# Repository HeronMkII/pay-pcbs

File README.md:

# Payload Subsystem PCBs
**PAY SSM V2**
**PAY LED V1**
**PAY SENSOR V1**

Schematic & PCB layout files for the Payload SSM. 

Layout done in KiCad.

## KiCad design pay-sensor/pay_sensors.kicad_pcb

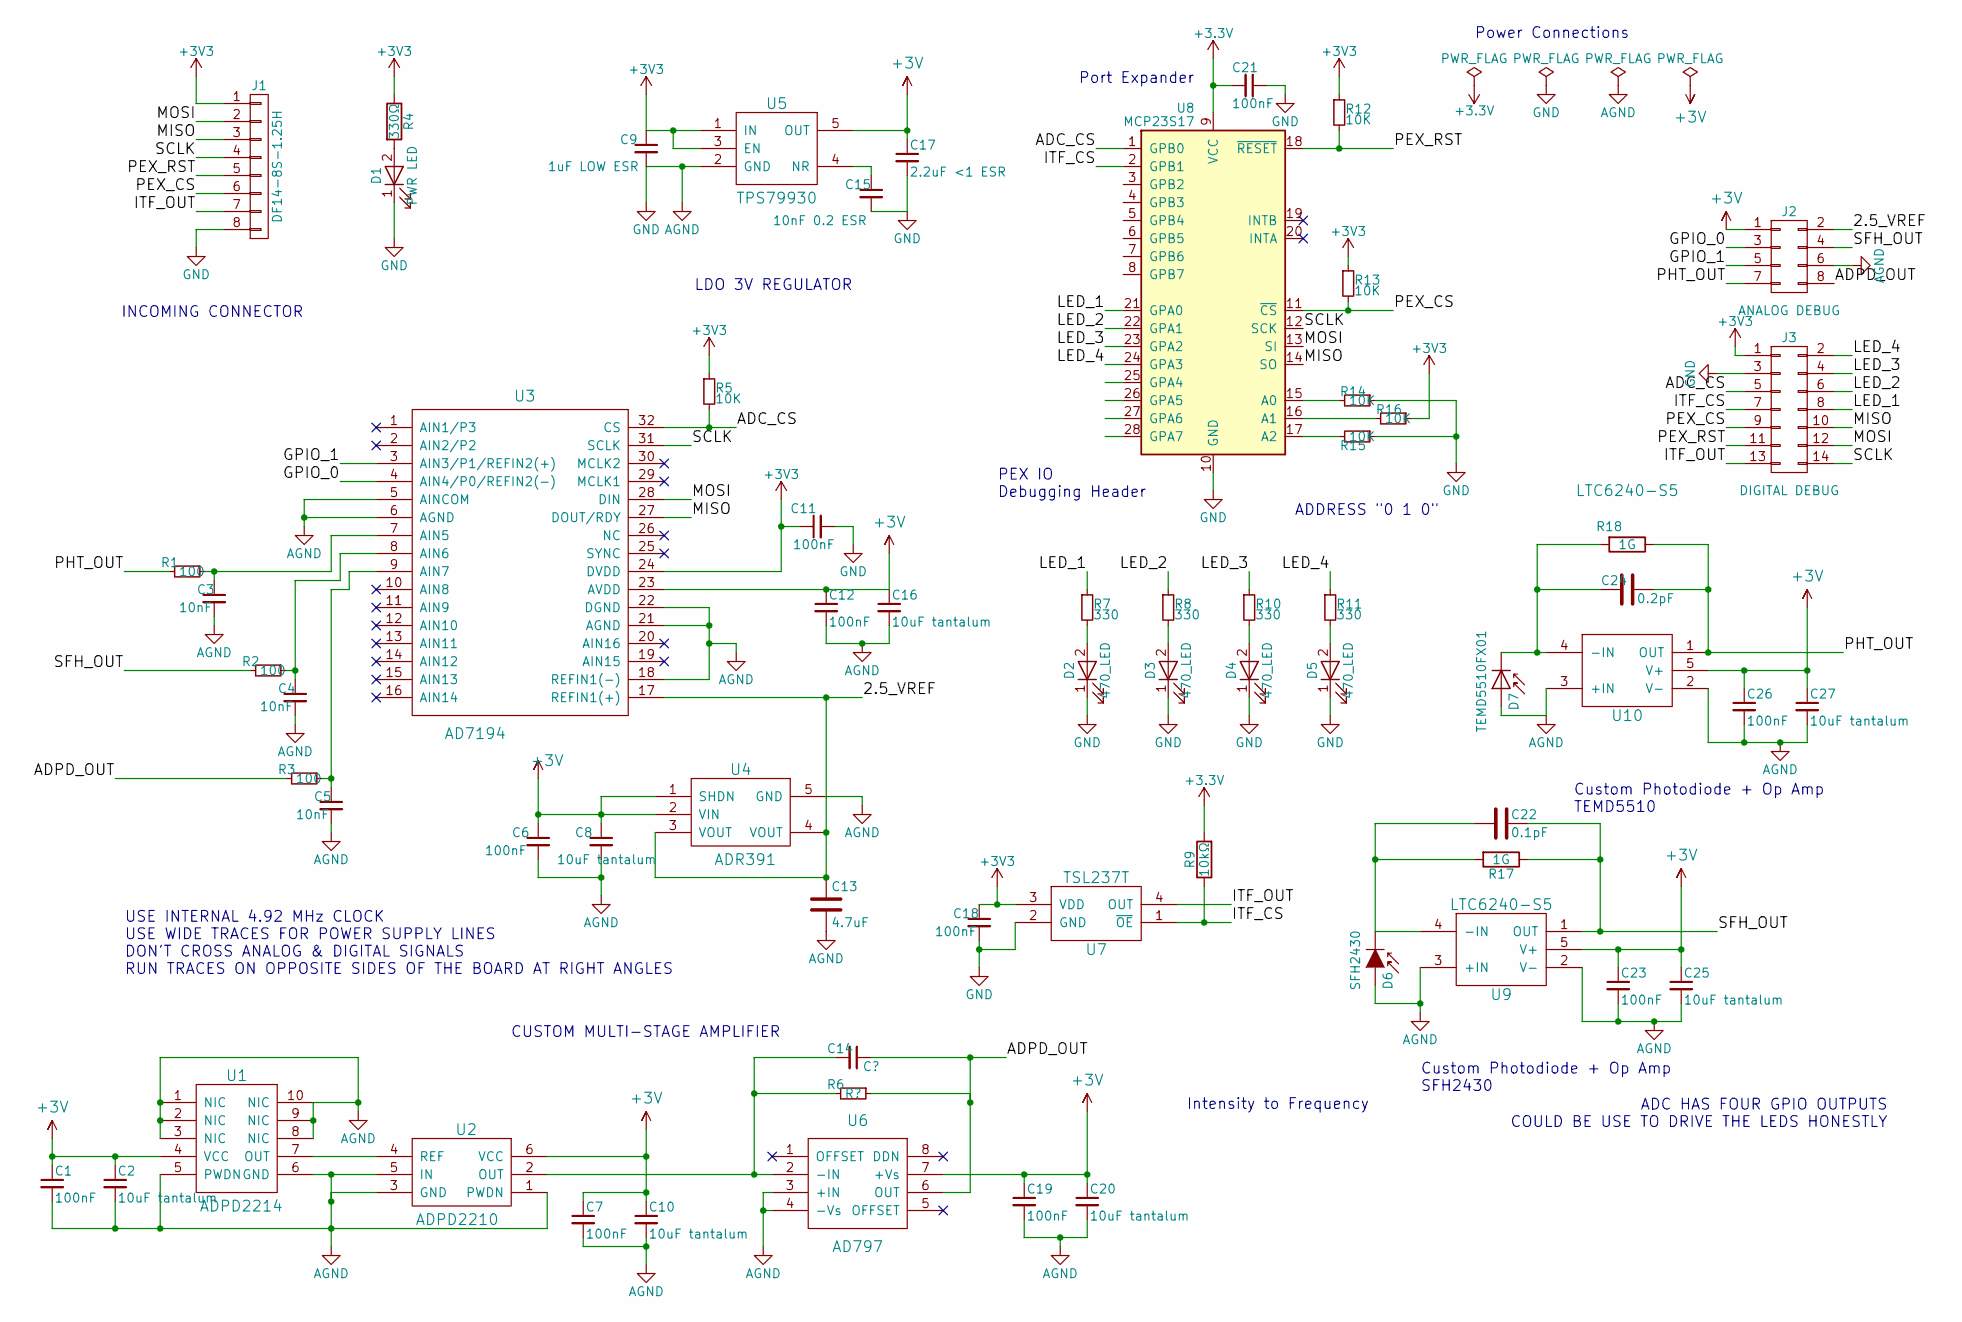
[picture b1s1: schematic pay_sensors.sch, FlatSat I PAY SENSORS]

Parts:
C1, C6, C7, C11, C12, C18, C19, C21, C23, C26: 100nF; C_0603
C2, C8, C10, C16, C20, C25, C27: 10uF tantalum; C_0603
C3, C4, C5: 10nF; C_0603
C9: 1uF LOW ESR; C_0603
C13: 4.7uF; C_0603
C14: C?; C_0603
C15: 10nF 0.2 ESR; C_0603
C17: 2.2uF <1 ESR; C_0603
C22: 0.1pF; C_0603
C24: 0.2pF; C_0603
D1: PWR LED; LED_0603
D2, D3, D4, D5: 470_LED; LED_0603
D6: SFH2430
D7: TEMD5510FX01; TEMD5510
J1: DF14-8S-1.25H; Hirose_DF14-8P-1.25H
J2: ANALOG DEBUG; Socket_Strip_Straight_2x04_Pitch2.54mm
J3: DIGITAL DEBUG; Socket_Strip_Straight_2x07_Pitch2.54mm
R1, R2, R3: 100; R_0603
R4: 330Ω; R_0603
R5, R12, R13, R14, R15, R16: 10K; R_0603
R6: R?; R_0603
R7, R8, R10, R11: 330; R_0603
R9: 10kΩ; R_0603
R17, R18: 1G; R_0603
U1: ADPD2214
U2: ADPD2210
U3: AD7194; QFN-32-1EP_5x5mm_Pitch0.5mm
U4: ADR391; SOT-23-5
U5: TPS79930; SOT-23-5
U6: AD797; SOIC-8_3.9x4.9mm_Pitch1.27mm
U7: TSL237T
U8: MCP23S17; SSOP-28_5.3x10.2mm_Pitch0.65mm
U9, U10: LTC6240-S5; SOT-23-5

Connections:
+3V: C1.1, C2.1, C6.1, C7.1, C8.1, C10.1, C12.1, C16.1, C17.1, C19.1, C20.1, C23.1, C25.1, C26.1, C27.1, J2.1, U1.4 (VCC), U2.6 (VCC), U3.23 (AVDD), U4.1 (SHDN), U4.2 (VIN), U5.5 (OUT), U6.7 (+Vs), U9.5 (V+), U10.5 (V+)
/2.5_VREF: C13.1, J2.2, U3.17 (REFIN1(+)), U4.3 (VOUT), U4.4 (VOUT)
/ADC_CS: J3.5, R5.2, U3.32 (CS), U8.1 (GPB0)
/ADPD_OUT: C14.1, J2.8, R3.2, R6.1, U6.6 (OUT)
/GPIO_0: J2.3, U3.4 (AIN4/P0/REFIN2(-))
/GPIO_1: J2.5, U3.3 (AIN3/P1/REFIN2(+))
/ITF_CS: J3.7, R9.1, U7.1 (~OE), U8.2 (GPB1)
/ITF_OUT: J1.7, J3.13, U7.4 (OUT)
/LED_1: J3.8, R7.1, U8.21 (GPA0)
/LED_2: J3.6, R8.1, U8.22 (GPA1)
/LED_3: J3.4, R10.1, U8.23 (GPA2)
/LED_4: J3.2, R11.1, U8.24 (GPA3)
/MISO: J1.3, J3.10, U3.27 (DOUT/RDY), U8.14 (SO)
/MOSI: J1.2, J3.12, U3.28 (DIN), U8.13 (SI)
/PEX_CS: J1.6, J3.9, R13.2, U8.11 (~CS)
/PEX_RST: J1.5, J3.11, R12.2, U8.18 (~RESET)
/PHT_OUT: C24.1, J2.7, R1.2, R18.1, U10.1 (OUT)
/SCLK: J1.4, J3.14, U3.31 (SCLK), U8.12 (SCK)
/SFH_OUT: C22.1, J2.4, R2.2, R17.1, U9.1 (OUT)
AGND: C1.2, C2.2, C3.2, C4.2, C5.2, C6.2, C7.2, C8.2, C9.2, C10.2, C11.2, C12.2, C13.2, C15.2, C16.2, C17.2, C18.2, C19.2, C20.2, C21.1, C23.2, C25.2, C26.2, C27.2, D1.1 (K), D2.1 (K), D3.1 (K), D4.1 (K), D5.1 (K), D6.2 (A), D7.2 (A), J1.8, J2.6, J3.3, R14.1, R15.1, U1.1 (NIC), U1.2 (NIC), U1.3 (NIC), U1.5 (PWDN), U1.6 (GND), U1.8 (NIC), U1.9 (NIC), U1.10 (NIC), U2.1 (PWDN), U2.3 (GND), U2.5 (IN), U3.5 (AINCOM), U3.6 (AGND), U3.18 (REFIN1(-)), U3.21 (AGND), U3.22 (DGND), U4.5 (GND), U5.2 (GND), U6.3 (+IN), U6.4 (-Vs), U7.2 (GND), U8.10 (GND), U9.2 (V-), U9.3 (+IN), U10.2 (V-), U10.3 (+IN)
unnamed: C3.1, R1.1, U3.7 (AIN5)
unnamed: C4.1, R2.1, U3.8 (AIN6)
unnamed: C5.1, R3.1, U3.9 (AIN7)
unnamed: C14.2, R6.2, U2.2 (OUT), U6.2 (-IN)
unnamed: C15.1, U5.4 (NR)
unnamed: C22.2, D6.1 (K), R17.2, U9.4 (-IN)
unnamed: C24.2, D7.1 (K), R18.2, U10.4 (-IN)
unnamed: D1.2 (A), R4.2
unnamed: D2.2 (A), R7.2
unnamed: D3.2 (A), R8.2
unnamed: D4.2 (A), R10.2
unnamed: D5.2 (A), R11.2
unnamed: R14.2, U8.15 (A0)
unnamed: R15.2, U8.17 (A2)
unnamed: R16.2, U8.16 (A1)
unnamed: U1.7 (OUT), U2.4 (REF)

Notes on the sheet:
Port Expander
Power Connections
Custom Photodiode + Op Amp TEMD5510
PEX IO Debugging Header
ADDRESS "0 1 0"
INCOMING CONNECTOR
LDO 3V REGULATOR
USE INTERNAL 4.92 MHz CLOCK USE WIDE TRACES FOR POWER SUPPLY LINES DON'T CROSS ANALOG & DIGITAL SIGNALS RUN TRACES ON OPPOSITE SIDES OF THE BOARD AT RIGHT ANGLES
CUSTOM MULTI-STAGE AMPLIFIER
ADC HAS FOUR GPIO OUTPUTS COULD BE USE TO DRIVE THE LEDS HONESTLY
Custom Photodiode + Op Amp SFH2430
Intensity to Frequency

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
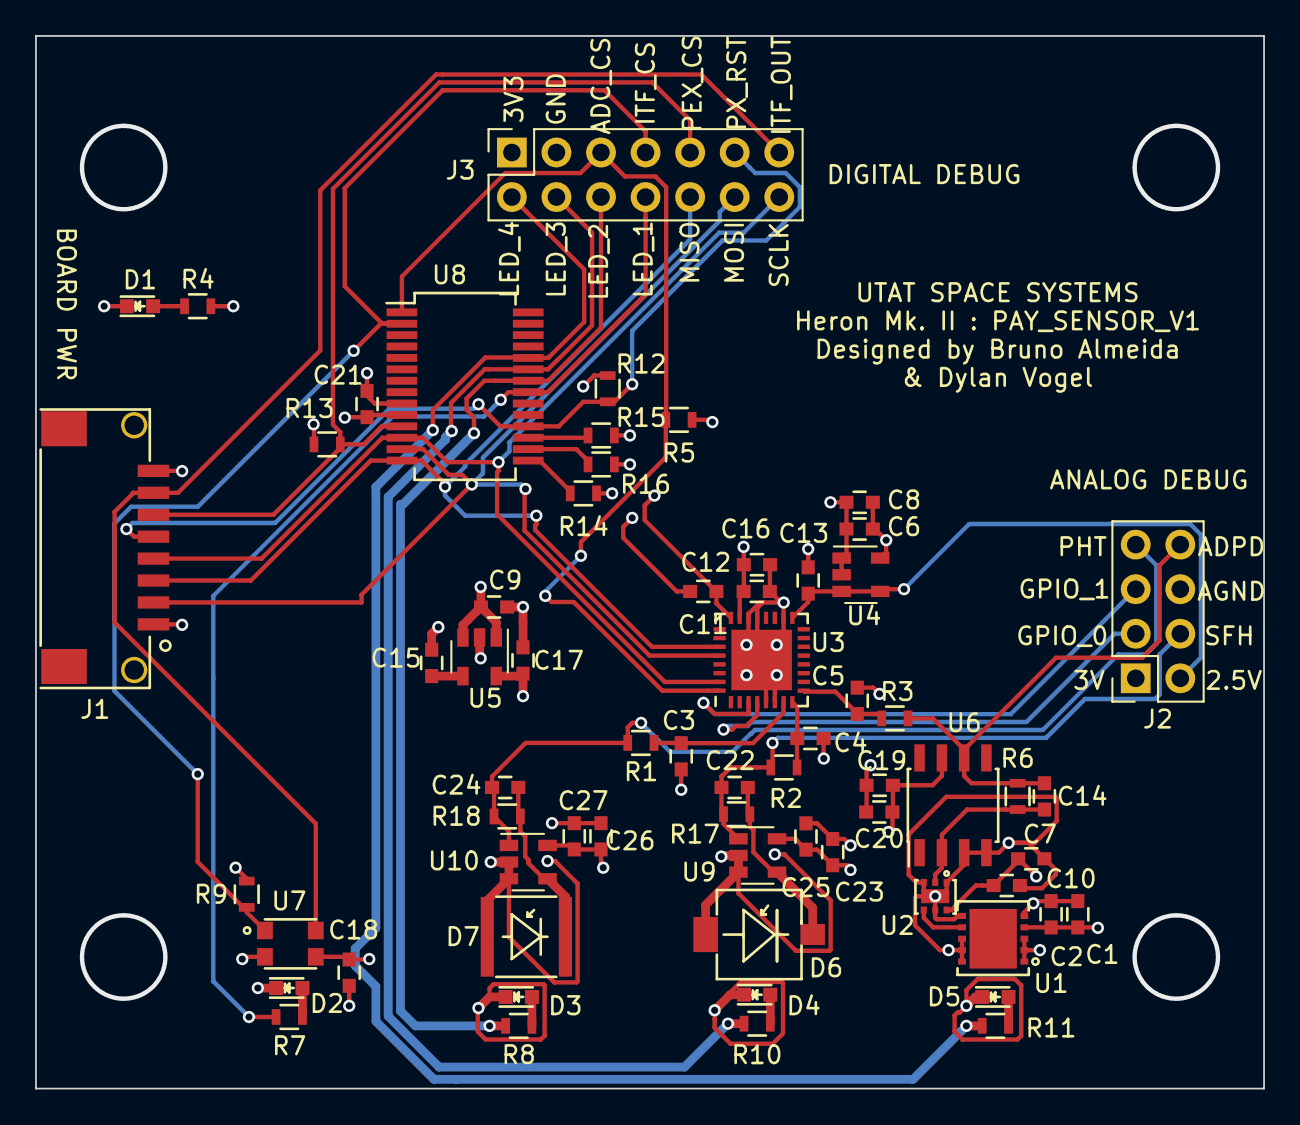
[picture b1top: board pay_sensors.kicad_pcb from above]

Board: 4 copper layers, 70.0 x 60.0 mm, 65 parts (0 on the bottom side), 37 nets.

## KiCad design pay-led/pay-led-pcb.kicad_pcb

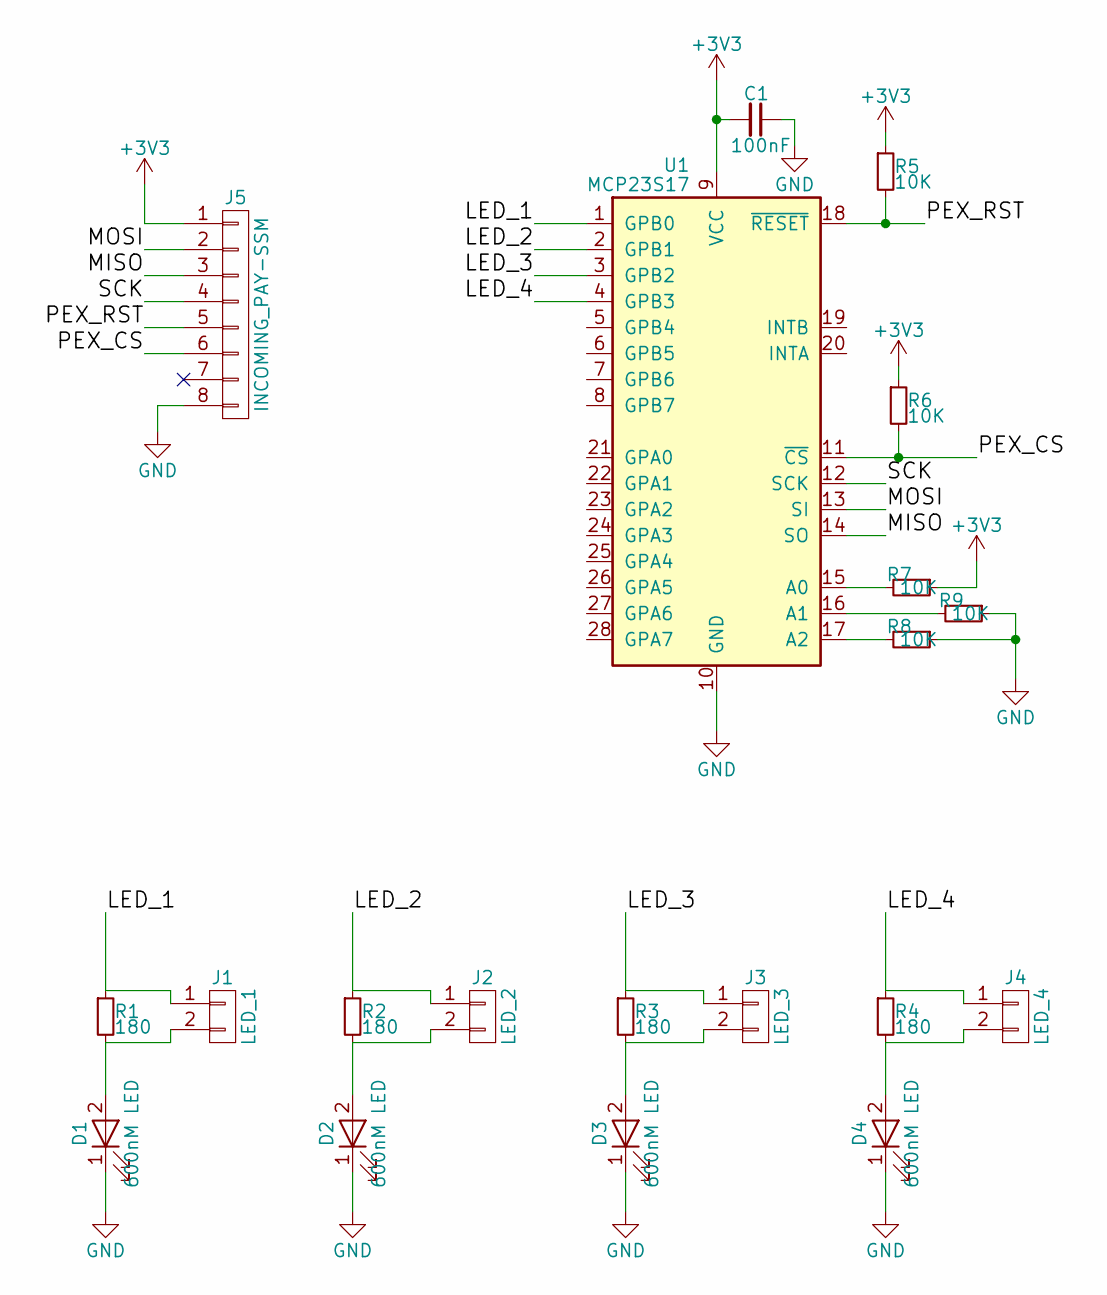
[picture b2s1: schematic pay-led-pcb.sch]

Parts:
C1: 100nF; C_0603
D1, D2, D3, D4: 600nM LED; LED_0603
J1: LED_1; Socket_Strip_Straight_1x02_Pitch2.54mm
J2: LED_2; Socket_Strip_Straight_1x02_Pitch2.54mm
J3: LED_3; Socket_Strip_Straight_1x02_Pitch2.54mm
J4: LED_4; Socket_Strip_Straight_1x02_Pitch2.54mm
J5: INCOMING_PAY-SSM; Hirose_DF14-8P-1.25H
R1, R2, R3, R4: 180; R_0603
R5, R6, R7, R8, R9: 10K; R_0603
U1: MCP23S17; SSOP-28_5.3x10.2mm_Pitch0.65mm

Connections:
+3V3: C1.2, J5.1, R5.1, R6.1, R7.1, U1.9 (VCC)
/LED_1: J1.1, R1.1, U1.1 (GPB0)
/LED_2: J2.1, R2.1, U1.2 (GPB1)
/LED_3: J3.1, R3.1, U1.3 (GPB2)
/LED_4: J4.1, R4.1, U1.4 (GPB3)
/MISO: J5.3, U1.14 (SO)
/MOSI: J5.2, U1.13 (SI)
/PEX_CS: J5.6, R6.2, U1.11 (~CS)
/PEX_RST: J5.5, R5.2, U1.18 (~RESET)
/SCK: J5.4, U1.12 (SCK)
GND: C1.1, D1.1 (K), D2.1 (K), D3.1 (K), D4.1 (K), J5.8, R8.1, R9.1, U1.10 (GND)
unnamed: D1.2 (A), J1.2, R1.2
unnamed: D2.2 (A), J2.2, R2.2
unnamed: D3.2 (A), J3.2, R3.2
unnamed: D4.2 (A), J4.2, R4.2
unnamed: R7.2, U1.15 (A0)
unnamed: R8.2, U1.17 (A2)
unnamed: R9.2, U1.16 (A1)

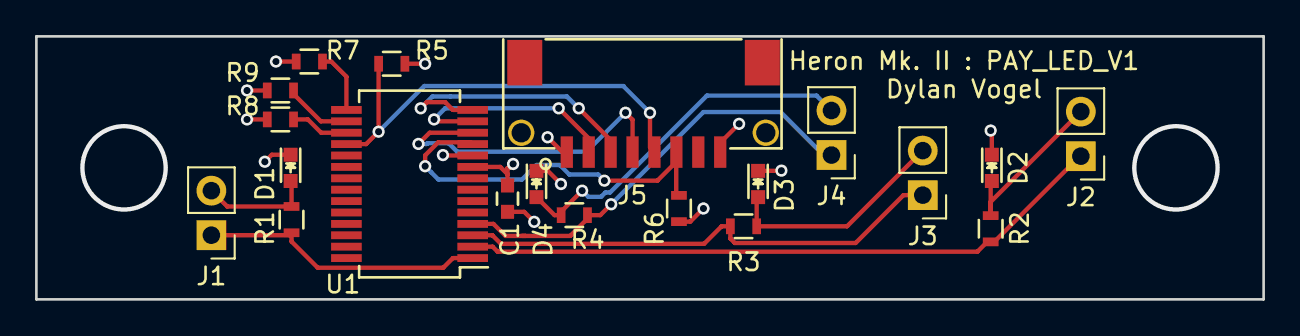
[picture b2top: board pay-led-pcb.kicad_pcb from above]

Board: 4 copper layers, 70.0 x 15.0 mm, 20 parts (0 on the bottom side), 18 nets.

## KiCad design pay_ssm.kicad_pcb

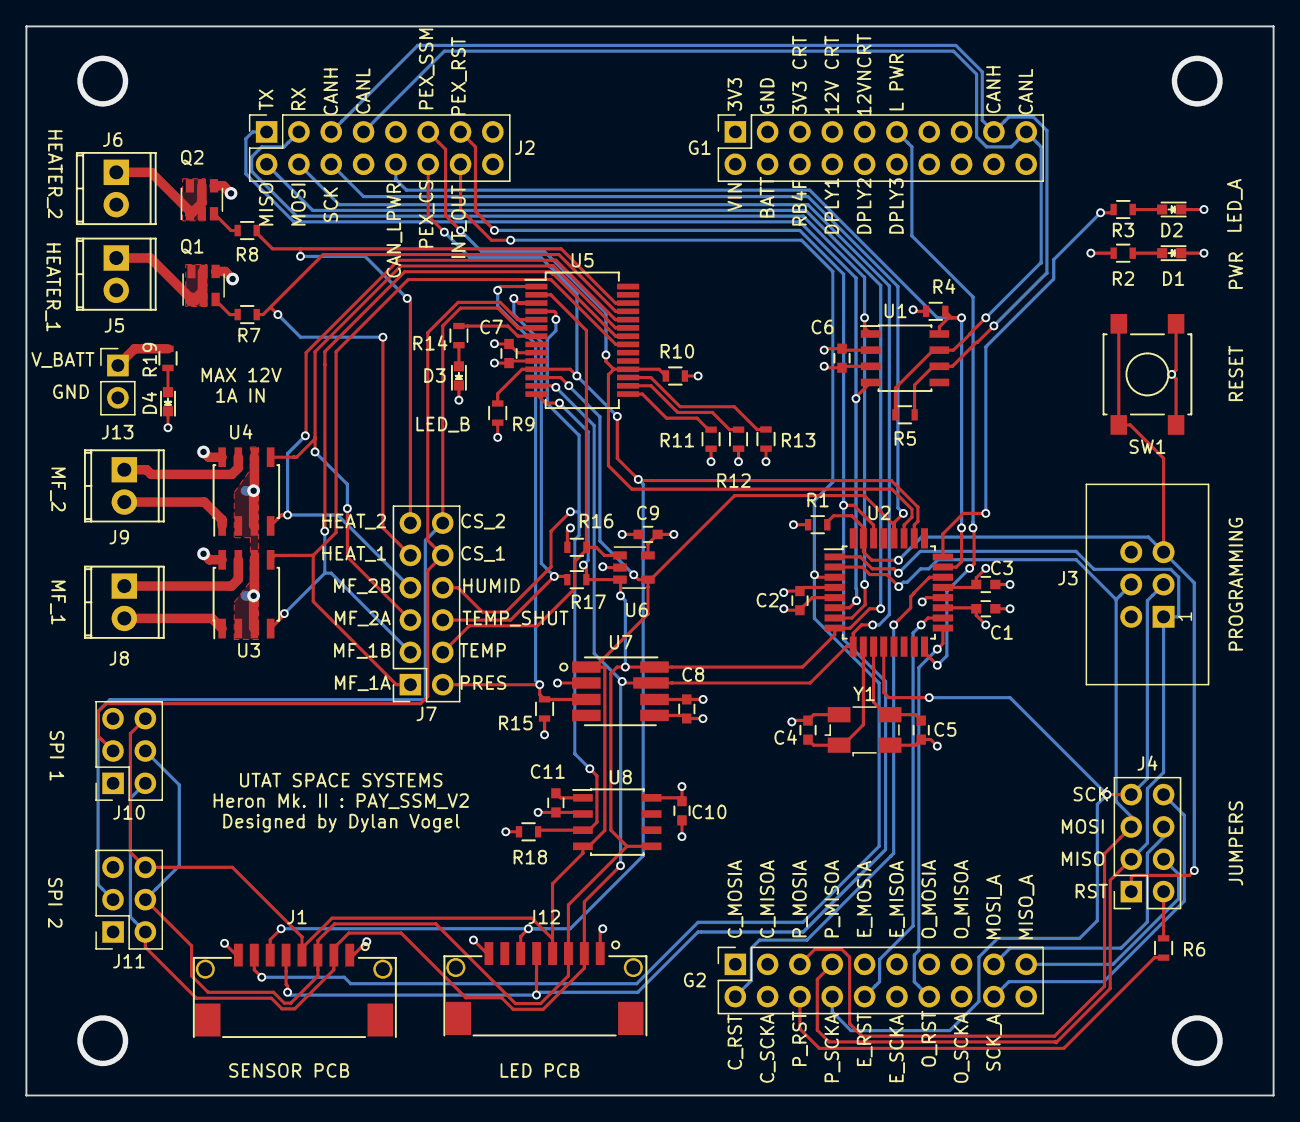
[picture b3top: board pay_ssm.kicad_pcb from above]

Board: 4 copper layers, 98.0 x 84.0 mm, 61 parts (0 on the bottom side), 60 nets.

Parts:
C1, C2, C3: 0.1 uF; C_0603
C4, C5: 22pF; C_0603
C6: 0.1uF; C_0603
C7, C8, C9, C11: 100nF; C_0603
C10: 0.22uF; C_0603
D1: PWR_LED; LED_0603
D2, D3: LED; LED_0603
D4: V_BATT_LED; LED_0603
G1: GENERAL CONN 1; Socket_Strip_Straight_2x10_Pitch2.54mm
G2: GENERAL CONN 2; Socket_Strip_Straight_2x10_Pitch2.54mm
J1, J12: CONN_01X08; Hirose_DF14-8P-1.25H
J2: DEBUG CONN; Socket_Strip_Straight_2x08_Pitch2.54mm
J3: PROGRAMMING PORT; IDC_Header_Straight_6pins
J4: RST_JMP; Socket_Strip_Straight_2x04_Pitch2.54mm
J5: HEATER_1; TerminalBlock_Pheonix_MPT-2.54mm_2pol
J6: HEATER_2; TerminalBlock_Pheonix_MPT-2.54mm_2pol
J7: SENSOR & SPI DEBUG; Socket_Strip_Straight_2x06_Pitch2.54mm
J8: MF_1; TerminalBlock_Pheonix_MPT-2.54mm_2pol
J9: MF_2; TerminalBlock_Pheonix_MPT-2.54mm_2pol
J10, J11: CONN_02X03; Socket_Strip_Straight_2x03_Pitch2.54mm
J13: CONN_01X02; Socket_Strip_Straight_1x02_Pitch2.54mm
Q1, Q2: FCD637BNZ; SOT-23-6
R1, R9, R10, R11, R12, R13, R15, R16, R17, R18, R19: 10K; R_0603
R2, R5, R6: 120R; R_0603
R3, R14: 220; R_0603
R4: 1K; R_0603
R7, R8: 5K; R_0603
SW1: SW_RST; SW_SPST_B3S-1000
U1: SN65HVD230; SOIC-8_3.9x4.9mm_Pitch1.27mm
U2: ATMEGA32M1-MU; TQFP-32_7x7mm_Pitch0.8mm
U3, U4: BD6231F; SOIC-8_3.9x4.9mm_Pitch1.27mm
U5: MCP23S17; SSOP-28_5.3x10.2mm_Pitch0.65mm
U6: LM95071; SOT-23-5
U7: MS580301BA01; MS580301BA
U8: HIH7131; SOIC-8_3.9x4.9mm_Pitch1.27mm
Y1: 8MHz; Crystal_SMD_Abracon_ABM3B-4pin_5.0x3.2mm

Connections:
+3V3: C1.2, C2.2, C3.2, C6.1, C7.2, C8.1, C9.1, C10.1, G1.1, J1.1, J3.2, J10.1, J11.1, J12.1, R1.1, R2.1, R9.1, R10.1, R15.2, R16.2, R18.1, U1.3, U2.4, U2.19, U2.21, U5.9, U6.5, U7.5, U8.8
/32M1_LED: R3.1, U2.24
/CANH: G1.17, J2.5, R5.1, U1.6
/CANL: G1.19, J2.7, R5.2, U1.7
/CAN_LPWR: J2.10, R4.2, U1.8, U2.23
/COM_RST: G2.2, U2.22
/EPS_RST: G2.10, U2.18
/INT_OUT: J1.7, J2.14, U2.3
/LOPWR: G1.11, U2.16
/MISO: J1.3, J2.2, J10.4, J11.4, J12.3, R17.1, U2.8, U5.14, U6.3, U7.8, U8.5
/MISO_A: G2.7, J3.1, J4.3, U2.1
/MISO_A_COMMON: G2.19, J4.4
/MOSI: J1.2, J2.4, J10.2, J11.2, J12.2, U2.9, U5.13, U7.7
/MOSI_A: G2.5, J3.4, J4.5, U2.2
/MOSI_A_COMMON: G2.17, J4.6
/OBC_RST: G2.14, U2.17
/PAY_RST: G2.6, R6.1
/PEX_CS: J1.6, J2.12, J12.6, R9.2, U2.26, U5.11
/PEX_RST: J1.5, J2.13, J12.5, U2.30
/PEX_SSM_RST: J2.11, R10.2, U2.27, U5.18
/RST: J3.5, J4.1, R1.2, SW1.1, U2.31
/RX_CAN: J2.3, U1.1, U2.7
/SCK: J1.4, J2.6, J10.6, J11.6, J12.4, U2.28, U5.12, U6.4, U7.1, U8.4
/SCK_A: G2.8, J3.3, J4.7, U2.12
/SCK_A_COMMON: G2.18, J4.8
/Sensors & SPI/CS_1: J7.10, J10.3, U5.5
/Sensors & SPI/CS_2: J7.12, J11.3, U5.6
/Sensors & SPI/HEATER_1: J7.9, R7.2, U5.25
/Sensors & SPI/HEATER_2: J7.11, R8.2, U5.26
/Sensors & SPI/HUMID_CS: J7.8, R18.2, U5.4, U8.3
/Sensors & SPI/MF_1A: J7.1, U3.5, U5.21
/Sensors & SPI/MF_1B: J7.3, U3.4, U5.22
/Sensors & SPI/MF_2A: J7.5, U4.5, U5.23
/Sensors & SPI/MF_2B: J7.7, U4.4, U5.24
/Sensors & SPI/PEX_LED: R14.1, U5.7
/Sensors & SPI/PRES_CS: J7.2, R15.1, U5.1, U7.3
/Sensors & SPI/TEMP_CS: J7.4, R16.1, U5.2, U6.1
/Sensors & SPI/TEMP_SHUTDOWN: J7.6, R17.2, U5.3
/TX_CAN: J2.1, U1.4, U2.6
/V_BATT: J5.2, J6.2, J13.1, R19.1, U3.2, U3.3, U3.6, U4.2, U4.3, U4.6
GND: C1.1, C2.1, C3.1, C4.1, C5.1, C6.2, C7.1, C8.2, C9.2, C10.2, C11.2, D1.1, D2.1, D3.1, D4.1, G1.3, J1.8, J3.6, J10.5, J11.5, J12.8, J13.2, Q1.3, Q2.3, R4.1, R11.1, R12.1, R13.2, SW1.2, U1.2, U2.5, U2.20, U3.8, U4.8, U5.10, U6.2, U7.2, U7.6, U8.2, Y1.2, Y1.4
unnamed: C4.2, U2.10, Y1.1
unnamed: C5.2, U2.11, Y1.3
unnamed: C11.1, U8.1
unnamed: D1.2, R2.2
unnamed: D2.2, R3.2
unnamed: D3.2, R14.2
unnamed: D4.2, R19.2
unnamed: J4.2, R6.2
unnamed: J5.1, Q1.1
unnamed: J6.1, Q2.1
unnamed: J8.1, U3.7
unnamed: J8.2, U3.1
unnamed: J9.1, U4.7
unnamed: J9.2, U4.1
unnamed: Q1.2, R7.1
unnamed: Q2.2, R8.1
unnamed: R11.2, U5.15
unnamed: R12.2, U5.17
unnamed: R13.1, U5.16

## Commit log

2017-08-20 Created a README
2017-08-20 Adding existing files
2017-08-20 Reverting README.md
2017-08-21 Finished the PAY SSM PCB layout.
2017-08-21 Edited silkscreen.
2017-08-21 Added gerber outputs.
2017-09-02 Merging the 3 PAY boards into one repository.
2017-09-02 Moving files.
2018-02-12 Update before Iteration3 Design - Added BOMs for previous iterotions
